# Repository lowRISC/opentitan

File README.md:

# OpenTitan

## About the project

[OpenTitan](https://opentitan.org) is an open source silicon Root of Trust (RoT) project.
OpenTitan will make the silicon RoT design and implementation more transparent, trustworthy, and secure for enterprises, platform providers, and chip manufacturers.
OpenTitan is administered by [lowRISC CIC](https://www.lowrisc.org) as a collaborative project to produce high quality, open IP for instantiation as a full-featured product.
See the [OpenTitan site](https://opentitan.org) and [OpenTitan docs](https://opentitan.org/book/) for more information about the project.

## About this repository

This repository contains hardware, software and utilities written as part of the OpenTitan project.
It is structured as monolithic repository, or "monorepo", where all components live in one repository.
It exists to enable collaboration across partners participating in the OpenTitan project.

## Documentation

The project contains comprehensive documentation of all IPs and tools.
You can access it [online at opentitan.org/book/](https://opentitan.org/book/).

## How to contribute

Have a look at [CONTRIBUTING](CONTRIBUTING.md) and our [documentation on project organization and processes](./doc/project_governance/README.md) for guidelines on how to contribute code to this repository.

## Licensing

Unless otherwise noted, everything in this repository is covered by the Apache License, Version 2.0 (see [LICENSE](https://github.com/lowRISC/opentitan/blob/master/LICENSE) for full text).

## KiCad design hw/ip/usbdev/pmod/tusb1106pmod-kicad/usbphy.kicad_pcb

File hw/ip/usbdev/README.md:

# USB 2.0 Full-Speed Device HWIP Technical Specification
<!-- BEGIN CMDGEN util/mdbook_regression_links.py --hjson hw/ip/usbdev/data/usbdev.hjson --top earlgrey -->
| Regression | Version | [Stages](https://opentitan.org/book/doc/project_governance/development_stages.html) | Results |
|-|-|-|-|
 [`usbdev`](https://dashboard.reports.lowrisc.org/opentitan/earlgrey/dashboard.html) | 2.1.0 | D2S, V2S |     |

This IP has been taped out in Earl Grey 1.0.0. The corresponding documentation and regression results can be found [here](https://opentitan.org/earlgrey_1.0.0/book/hw/ip/usbdev/index.html).

<!-- END CMDGEN -->

# Overview

This document specifies the USB device hardware IP functionality.
This IP block implements a Full-Speed device according to the [USB 2.0 specification.](https://www.usb.org/document-library/usb-20-specification)
It is attached to the chip interconnect bus as a peripheral module and conforms to the [Comportable guideline for peripheral functionality.](../../../doc/contributing/hw/comportability/README.md)

## Features

The IP block implements the following features:

- USB 2.0 Full-Speed (12 Mbps) Device interface
- 2 kB interface buffer
- Up to 12 endpoints (including required Endpoint 0), configurable using a compile-time Verilog parameter
- Support for USB packet sizes up to 64 bytes
- Support SETUP, IN and OUT transactions
- Support for Bulk, Control, Interrupt and Isochronous endpoints and transactions
- Streaming possible through software
- Interrupts for packet reception and transmission
- Flippable D+/D- pins, configurable via software, useful if it helps routing the PCB or if D+/D- are mapped to SBU1/SBU2 pins of USB-C

Isochronous transfers larger than 64 bytes are currently not supported.
This feature might be added in a later version of this IP.

## Description

The USB device module is a simple software-driven generic USB device interface for Full-Speed USB 2.0 operation.
The IP includes the physical layer interface, the low level USB protocol and a packet buffer interface to the software.
The physical layer interface features multiple transmit and receive paths to allow interfacing with a variety of USB PHYs or regular 3.3V IO pads for FPGA prototyping.

## Compatibility

The USB device programming interface is not based on any existing interface.

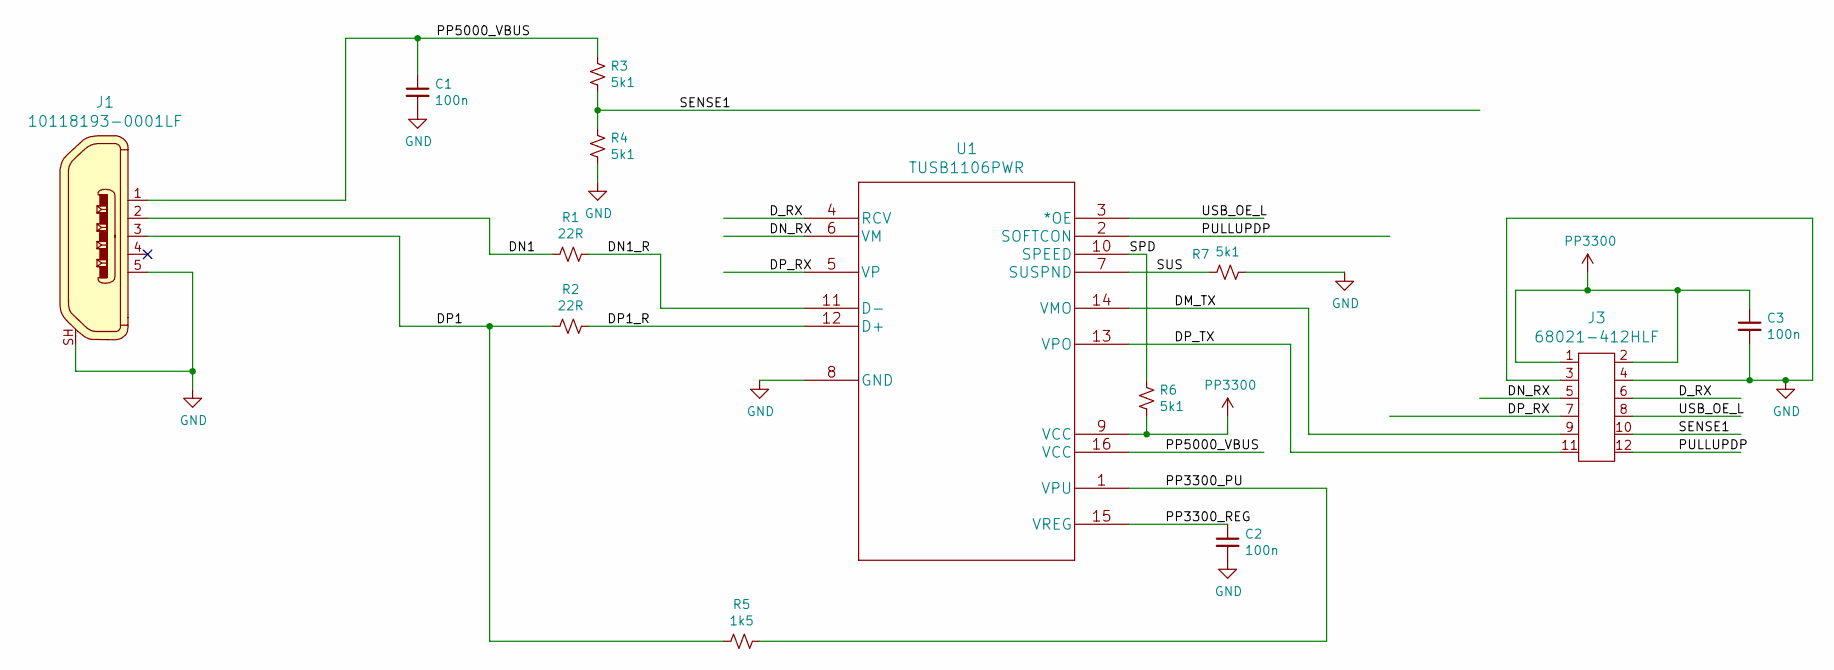
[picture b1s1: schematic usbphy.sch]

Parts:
C1, C2, C3: 100n; C_0805_2012Metric_Pad1.15x1.40mm_HandSolder
J1: 10118193-0001LF; USB_Micro_B_Female_10118193-0001LF; MPN 10118193-0001LF; Digi-Key_PN 609-4616-1-ND
J3: 68021-412HLF; PinHeader_6x2_P2.54mm_Horizontal; MPN 68021-412HLF; Digi-Key_PN 609-3355-ND
R1, R2: 22R; R_0805_2012Metric_Pad1.15x1.40mm_HandSolder
R3, R4, R6, R7: 5k1; R_0805_2012Metric_Pad1.15x1.40mm_HandSolder
R5: 1k5; R_0805_2012Metric_Pad1.15x1.40mm_HandSolder
U1: TUSB1106PWR

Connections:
/DM_TX: J3.9, U1.14 (VMO)
/DN1: J1.2, R1.2
/DN1_R: R1.1, U1.11 (D-)
/DN_RX: J3.5, U1.6 (VM)
/DP1: J1.3, R2.2, R5.2
/DP1_R: R2.1, U1.12 (D+)
/DP_RX: J3.7, U1.5 (VP)
/DP_TX: J3.11, U1.13 (VPO)
/D_RX: J3.6, U1.4 (RCV)
/PP3300_PU: R5.1, U1.1 (VPU)
/PP3300_REG: C2.1, U1.15 (VREG)
/PP5000_VBUS: C1.1, J1.1, R3.1, U1.16 (VCC)
/PULLUPDP: J3.12, U1.2 (SOFTCON)
/SENSE1: J3.10, R3.2, R4.1
/SPD: R6.1, U1.10 (SPEED)
/SUS: R7.2, U1.7 (SUSPND)
/USB_OE_L: J3.8, U1.3 (*OE)
GND: C1.2, C2.2, C3.2, J1.5, J1.SH, J3.3, J3.4, R4.2, R7.1, U1.8 (GND)
PP3300: C3.1, J3.1, J3.2, R6.2, U1.9 (VCC)

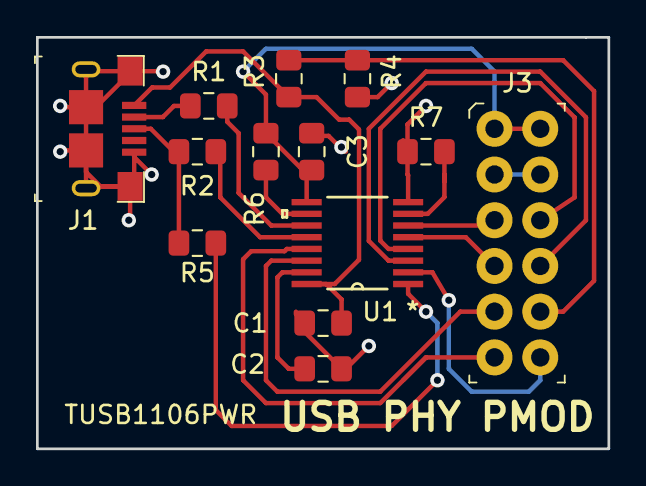
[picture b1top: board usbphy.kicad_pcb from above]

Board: 2 copper layers, 31.8 x 22.9 mm, 13 parts (0 on the bottom side), 19 nets.

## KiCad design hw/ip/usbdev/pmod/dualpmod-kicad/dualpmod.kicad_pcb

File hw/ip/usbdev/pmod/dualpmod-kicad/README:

// Copyright lowRISC contributors (OpenTitan project).
// Licensed under the Apache License, Version 2.0, see LICENSE for details.
// SPDX-License-Identifier: Apache-2.0

These files are the KiCad Version 5 CAD files for the PMOD that allows
one or two instances of the usbdev interface to be tested on boards
like the Nexys Video that have PMOD connectors with no internal series
resistor on the data lines.

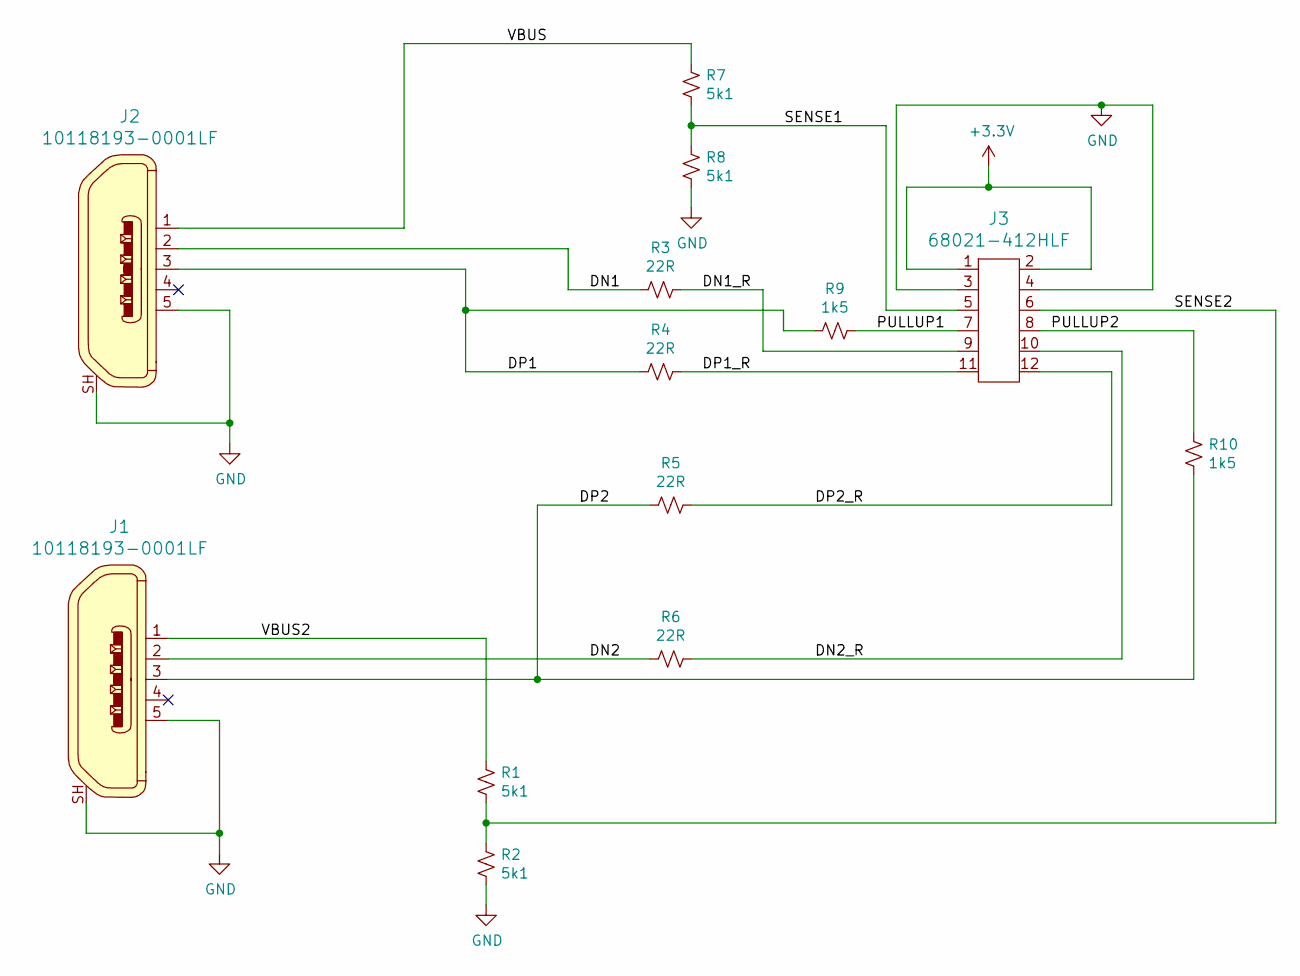
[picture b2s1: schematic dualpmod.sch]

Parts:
J1, J2: 10118193-0001LF; USB_Micro_B_Female_10118193-0001LF; MPN 10118193-0001LF; Digi-Key_PN 609-4616-1-ND
J3: 68021-412HLF; PinHeader_6x2_P2.54mm_Horizontal; MPN 68021-412HLF; Digi-Key_PN 609-3355-ND
R1, R2, R7, R8: 5k1; R_0805_2012Metric_Pad1.15x1.40mm_HandSolder
R3, R4, R5, R6: 22R; R_0805_2012Metric_Pad1.15x1.40mm_HandSolder
R9, R10: 1k5; R_0805_2012Metric_Pad1.15x1.40mm_HandSolder

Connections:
+3V3: J3.1, J3.2
/DN1: J2.2, R3.2
/DN1_R: J3.9, R3.1
/DN2: J1.2, R6.2
/DN2_R: J3.10, R6.1
/DP1: J2.3, R4.2, R9.2
/DP1_R: J3.11, R4.1
/DP2: J1.3, R5.2, R10.2
/DP2_R: J3.12, R5.1
/PULLUP1: J3.7, R9.1
/PULLUP2: J3.8, R10.1
/SENSE1: J3.5, R7.2, R8.1
/SENSE2: J3.6, R1.2, R2.1
/VBUS: J2.1, R7.1
/VBUS2: J1.1, R1.1
GND: J1.5, J1.SH, J2.5, J2.SH, J3.3, J3.4, R2.2, R8.2

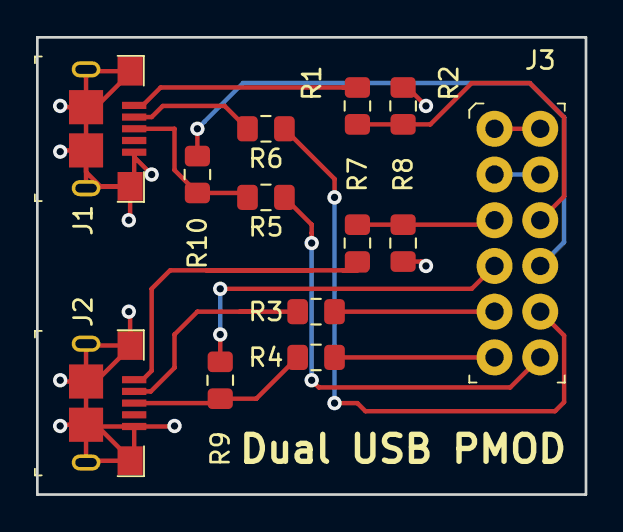
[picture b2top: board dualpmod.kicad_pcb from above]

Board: 2 copper layers, 30.5 x 25.4 mm, 13 parts (0 on the bottom side), 16 nets.

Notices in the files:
parts and their libraries:
Copyright 2016 Accelerated Designs. All rights reserved.
